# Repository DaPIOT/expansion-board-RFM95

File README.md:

# Expansion PCB for RFM95/96 module

> Only for testing and educational purposes

<div align="center">
   <br>
</div>

## Pinout
<div align="center">
   <br>
</div>

 > Support me by leaving a star at the upper right corner xD

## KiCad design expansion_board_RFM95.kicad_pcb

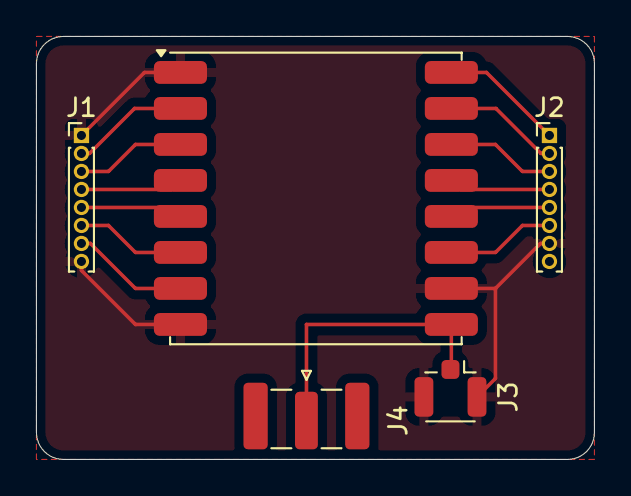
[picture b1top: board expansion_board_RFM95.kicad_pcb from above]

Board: 2 copper layers, 31.0 x 23.5 mm, 5 parts (0 on the bottom side), 14 nets.

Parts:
J1, J2: Conn_01x08_Pin; PinHeader_1x08_P1.00mm_Vertical
J3: U.FL-R-SMT_01_; U.FL_Hirose_U.FL-R-SMT-1_Vertical
J4: SMA-J-P-H-ST-EM1; SMA_Samtec_SMA-J-P-H-ST-EM1_EdgeMount
U1: RFM95W-915S2; HOPERF_RFM9XW_SMD

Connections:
/3.3V: J2.4, U1.13 (3.3V)
/DIO0: J2.3, U1.14 (DIO0)
/DIO1: J2.2, U1.15 (DIO1)
/DIO2: J2.1, U1.16 (DIO2)
/DIO3: J2.6, U1.11 (DIO3)
/DIO4: J2.5, U1.12 (DIO4)
/DIO5: J1.7, U1.7 (DIO5)
/MISO: J1.2, U1.2 (MISO)
/MOSI: J1.3, U1.3 (MOSI)
/NSS: J1.5, U1.5 (NSS)
/RESET: J1.6, U1.6 (RESET)
/SCK: J1.4, U1.4 (SCK)
/SIG: J3.1 (GND), J4.1, U1.9 (ANT)
GND: J1.1, J1.8, J2.7, J3.2 (GND), U1.1 (GND), U1.8 (GND), U1.10 (GND)

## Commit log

2025-02-06 expansion pcb for RFM95 module
2025-02-06 Adding illustration
2025-02-07 pinout
